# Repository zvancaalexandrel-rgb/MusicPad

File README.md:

# MusicPad
A 12 switch macropad with a rotary encoder and  .91" oled screen.

## BOM
 - 12x MX Style Switches
 - 4x M3x5mx4mm heatset inserts
 - 3D Printed case
 - 12x Blank DSA keycaps
 - 1x seeed studios xiao rp2040 sma version
 - 1x EC11 rotary encoder
 - 12x Through-hole 1N4148 Diodes
 - 1x knob
 - 4x SK6812 MINI-E LEDs
 - 12x MX Style Switches
 - 1x 0.91" oled screen
 - 4x M3x16mm screws

# What will i use it for
I would like to use it for different shortcuts for video games and listening for music on spotify 

# Photos

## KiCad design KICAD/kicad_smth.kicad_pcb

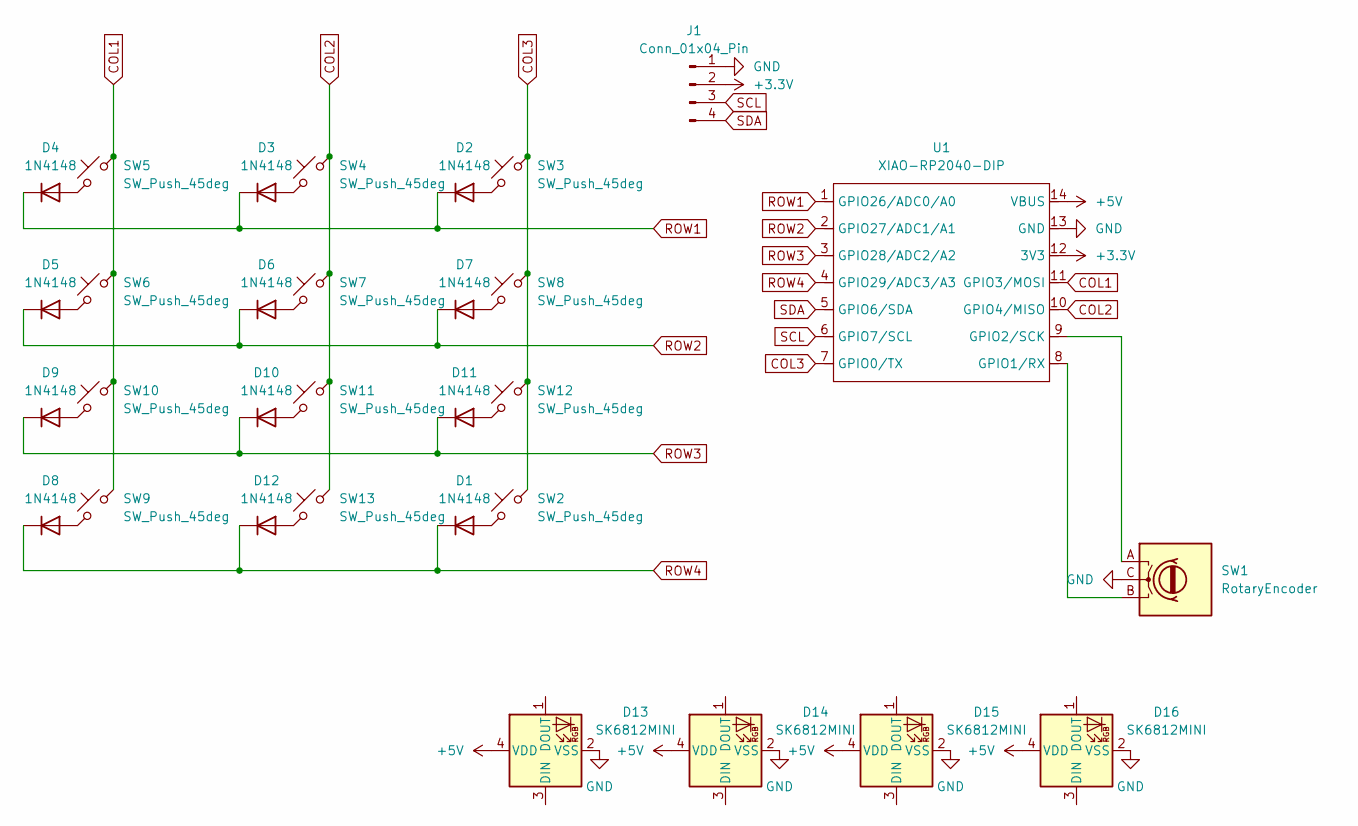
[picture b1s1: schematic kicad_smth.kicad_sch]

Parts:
D1, D2, D3, D4, D5, D6, D7, D8, D9, D10, D11, D12: 1N4148; D_DO-35_SOD27_P7.62mm_Horizontal
D13, D14, D15, D16: SK6812MINI; LED_SK6812MINI_PLCC4_3.5x3.5mm_P1.75mm
J1: Conn_01x04_Pin; SSD1306-0.91-OLED-4pin-128x32
SW1: RotaryEncoder; RotaryEncoder_Alps_EC11E-Switch_Vertical_H20mm
SW2, SW3, SW4, SW5, SW6, SW7, SW8, SW9, SW10, SW11, SW12, SW13: SW_Push_45deg; SW_Cherry_MX_1.00u_PCB
U1: XIAO-RP2040-DIP

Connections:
+3.3V: J1.2, U1.12 (3V3)
+5V: D13.4 (VDD), D14.4 (VDD), D15.4 (VDD), D16.4 (VDD), U1.14 (VBUS)
COL1: SW5.2, SW6.2, SW9.2, SW10.2, U1.11 (GPIO3/MOSI)
COL2: SW4.2, SW7.2, SW11.2, SW13.2, U1.10 (GPIO4/MISO)
COL3: SW2.2, SW3.2, SW8.2, SW12.2, U1.7 (GPIO0/TX)
GND: D13.2 (VSS), D14.2 (VSS), D15.2 (VSS), D16.2 (VSS), J1.1, SW1.C, U1.13 (GND)
unnamed: D1.2 (A), SW2.1
unnamed: D2.2 (A), SW3.1
unnamed: D3.2 (A), SW4.1
unnamed: D4.2 (A), SW5.1
unnamed: D5.2 (A), SW6.1
unnamed: D6.2 (A), SW7.1
unnamed: D7.2 (A), SW8.1
unnamed: D8.2 (A), SW9.1
unnamed: D9.2 (A), SW10.1
unnamed: D10.2 (A), SW11.1
unnamed: D11.2 (A), SW12.1
unnamed: D12.2 (A), SW13.1
unnamed: SW1.B, U1.8 (GPIO1/RX)
unnamed: SW1.A, U1.9 (GPIO2/SCK)
ROW1: D2.1 (K), D3.1 (K), D4.1 (K), U1.1 (GPIO26/ADC0/A0)
ROW2: D5.1 (K), D6.1 (K), D7.1 (K), U1.2 (GPIO27/ADC1/A1)
ROW3: D9.1 (K), D10.1 (K), D11.1 (K), U1.3 (GPIO28/ADC2/A2)
ROW4: D1.1 (K), D8.1 (K), D12.1 (K), U1.4 (GPIO29/ADC3/A3)
SCL: J1.3, U1.6 (GPIO7/SCL)
SDA: J1.4, U1.5 (GPIO6/SDA)

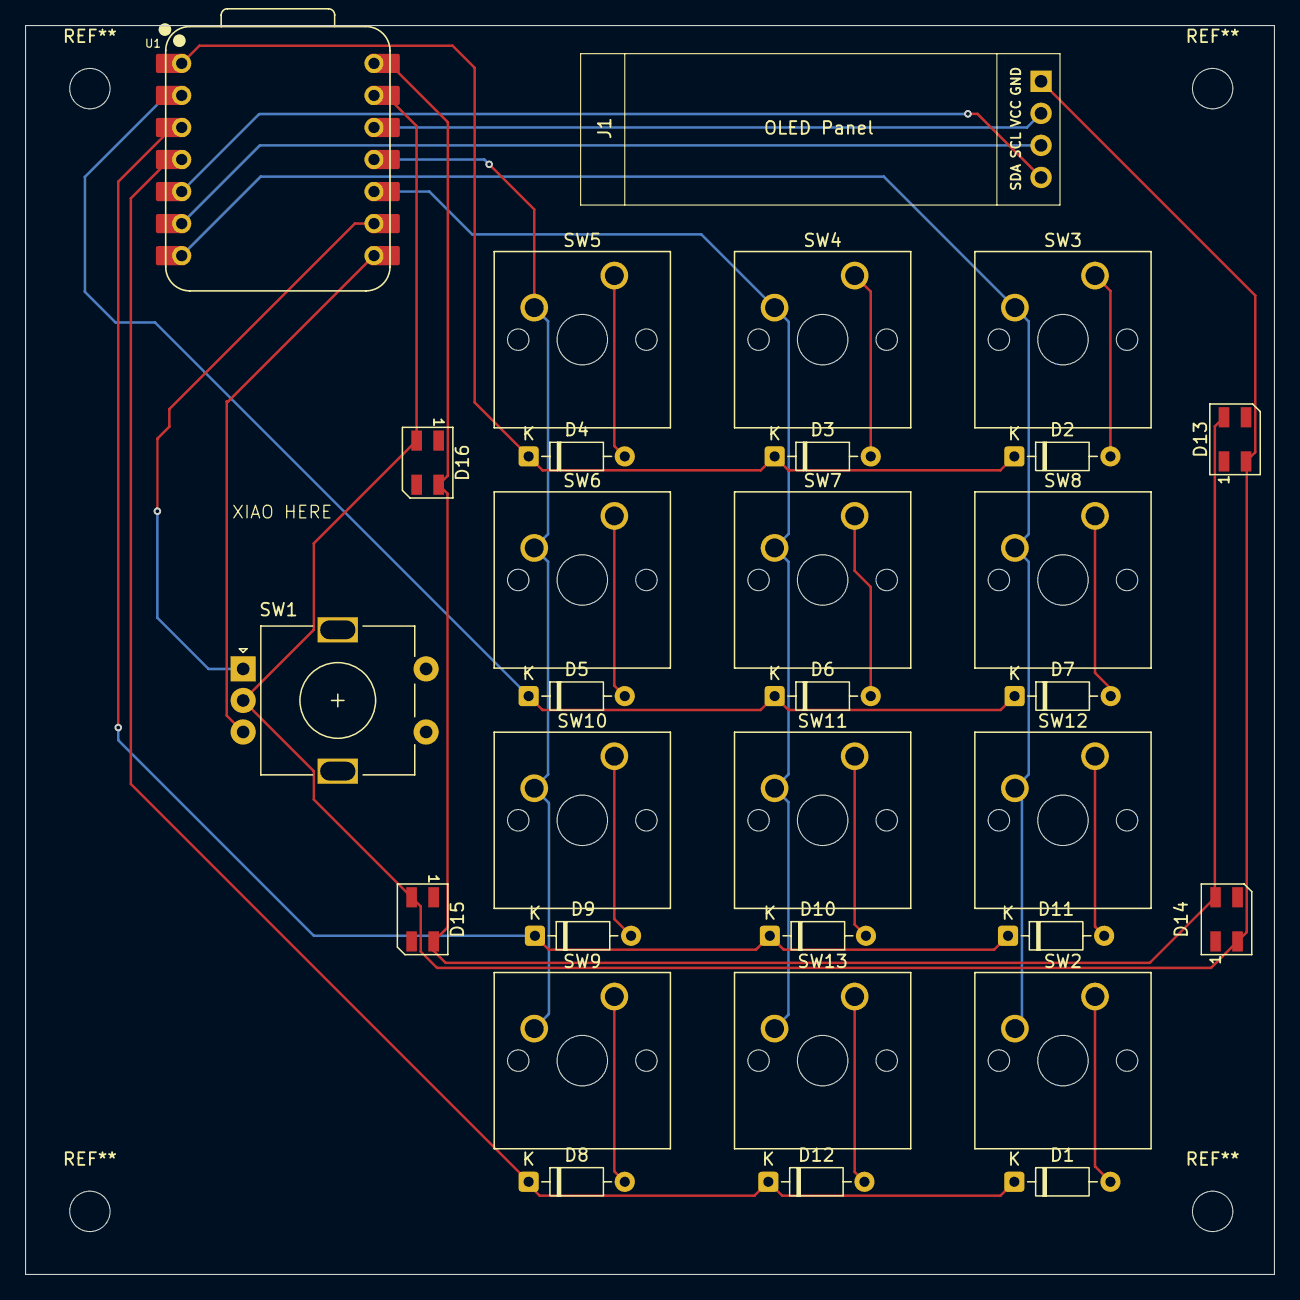
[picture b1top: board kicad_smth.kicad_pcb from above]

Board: 2 copper layers, 99.0 x 99.0 mm, 31 parts (0 on the bottom side), 26 nets.

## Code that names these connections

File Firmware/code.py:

import board
import busio
import adafruit_ssd1306
from kmk.kmk_keyboard import KMKKeyboard
from kmk.keys import KC
from kmk.scanners import DiodeOrientation
from kmk.modules.encoder import EncoderHandler
from kmk.extensions.media_keys import MediaKeys

# Initialize keyboard
keyboard = KMKKeyboard()

# Pin configuration for 4x3 matrix
# Columns: 3 pins
keyboard.col_pins = (board.D1, board.D2, board.D3)  # COL1, COL2, COL3
# Rows: 4 pins  
keyboard.row_pins = (board.D4, board.D5, board.D6, board.D7)  # ROW1, ROW2, ROW3, ROW4
keyboard.diode_orientation = DiodeOrientation.COL2ROW

# Add media keys extension
keyboard.extensions.append(MediaKeys())

# Encoder configuration
encoder_handler = EncoderHandler()
encoder_handler.pins = ((board.D9, board.D10, None, False),)  # Encoder on D9/D10
encoder_handler.map = [((KC.VOLD, KC.VOLU, KC.MUTE),)]  # Volume control with mute on press
keyboard.modules.append(encoder_handler)

# OLED Display initialization
try:
    i2c = busio.I2C(board.D11, board.D12)  # SCL=D11, SDA=D12
    display = adafruit_ssd1306.SSD1306_I2C(128, 32, i2c)
    display.fill(0)
    display.text('  CADPAD V2.0', 20, 4, 1)
    display.line(0, 16, 128, 16, 1)
    display.text('VOL: Encoder', 28, 20, 1)
    display.show()
except Exception as e:
    print(f"OLED Display Error: {e}")

# Keymap for 4 rows x 3 columns matrix layout:
# Row1: [D4] [D3] [D2]    (Col1, Col2, Col3)
# Row2: [D5] [D6] [D7]    (Col1, Col2, Col3)  
# Row3: [D9] [D10] [D11]  (Col1, Col2, Col3)
# Row4: [D8] [D12] [D1]   (Col1, Col2, Col3)

keyboard.keymap = [
    [KC.D4,  KC.D3,  KC.D2],   # Row 1 - Navigation/Function keys
    [KC.D5,  KC.D6,  KC.D7],   # Row 2 - Media/Control keys
    [KC.D9,  KC.D10, KC.D11],  # Row 3 - Shortcut/Action keys
    [KC.D8,  KC.D12, KC.D1]    # Row 4 - Utility/System keys
]

if __name__ == '__main__':
    keyboard.go()

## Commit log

2026-03-18 Create CAD
2026-03-18 Create PCB
2026-03-18 Create Firmware
2026-03-23 Create e
2026-03-23 Update README with project details and images
    Added a detailed description of the MusicPad project, including a bill of materials, usage, and photos.
2026-03-23 Revise BOM section in README.md
    Updated the Bill of Materials (BOM) section for clarity.
2026-03-25 Add keyboard firmware with OLED and encoder support
2026-03-25 Add boot configuration for 4x3 keyboard matrix
    Implement boot configuration for keyboard matrix to disable USB drive access during firmware updates.
